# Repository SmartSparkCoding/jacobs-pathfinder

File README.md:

# Jacob's (Amazing) Pathfinder

A Pathfinder, created with Stasis' Guides for Hack Club Stasis (and myself, of course!). I do follow the slides for some of this, even though I am working alone. 

## Pathfinder Session 1 - 1 hour

I created the schemtic for my Pathfinder. I also added my footprints ready for my next session. I am up to Slide 51 on the Workshop Guide. Here is what I did:

## Pathfinder Session 2 - 1 Hour and 15 Minutes

I converted my schematic into my PCB design, making sure that everything works correctly. I also added an extra button as my future plan is to have a three button game and the fourth to reset the game. 

## Pathfinder Session 3 - 1 Hour and 7 Minutes

Almost done! I just added all the 3D models to my PCB and started writing my code for the pathfinder! 

## Pathfinder Session 4 - 1 hour

Spent just 1 hour putting together all my code! Started some of it yesterday and just waiting for a sanity check from Slack!

## Pathfinder Session 5 - 10 Minutes

Made some simple PCB fixes and researched into adding the Hack Club logo to the PCB. Also made some quick changes to the code.

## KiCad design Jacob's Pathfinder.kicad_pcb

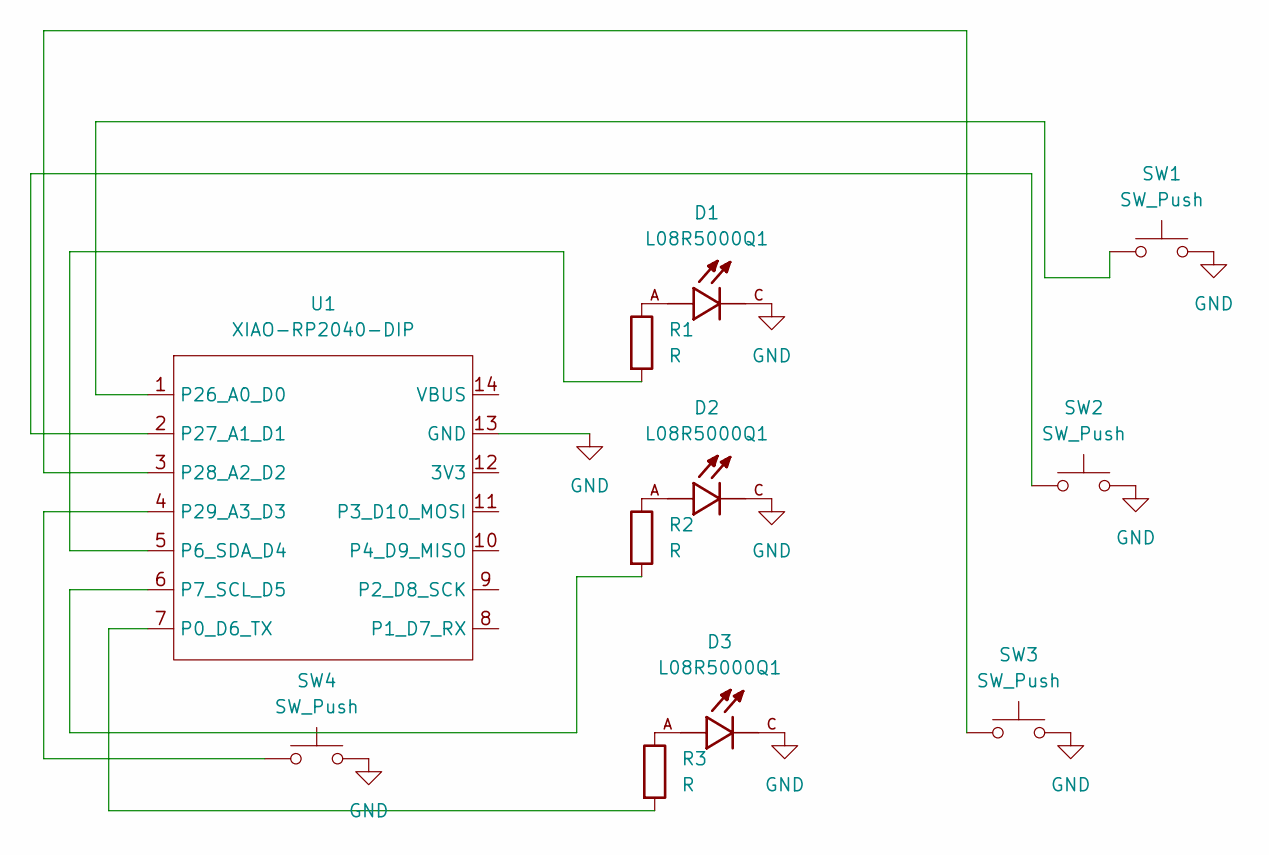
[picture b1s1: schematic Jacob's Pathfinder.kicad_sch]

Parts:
D1, D2, D3: L08R5000Q1; LEDRD254W57D500H1070; PARTREV NA
R1, R2, R3: R; R_Axial_DIN0204_L3.6mm_D1.6mm_P5.08mm_Horizontal
SW1, SW2, SW3, SW4: SW_Push; SW_Cherry_MX_1.00u_PCB
U1: XIAO-RP2040-DIP

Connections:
GND: D1.C, D2.C, D3.C, SW1.2, SW2.2, SW3.2, SW4.2, U1.13 (GND)
unnamed: D1.A, R1.1
unnamed: D2.A, R2.1
unnamed: D3.A, R3.1
unnamed: R3.2, U1.7 (P0_D6_TX)
unnamed: R1.2, U1.5 (P6_SDA_D4)
unnamed: R2.2, U1.6 (P7_SCL_D5)
unnamed: SW1.1, U1.1 (P26_A0_D0)
unnamed: SW2.1, U1.2 (P27_A1_D1)
unnamed: SW3.1, U1.3 (P28_A2_D2)
unnamed: SW4.1, U1.4 (P29_A3_D3)

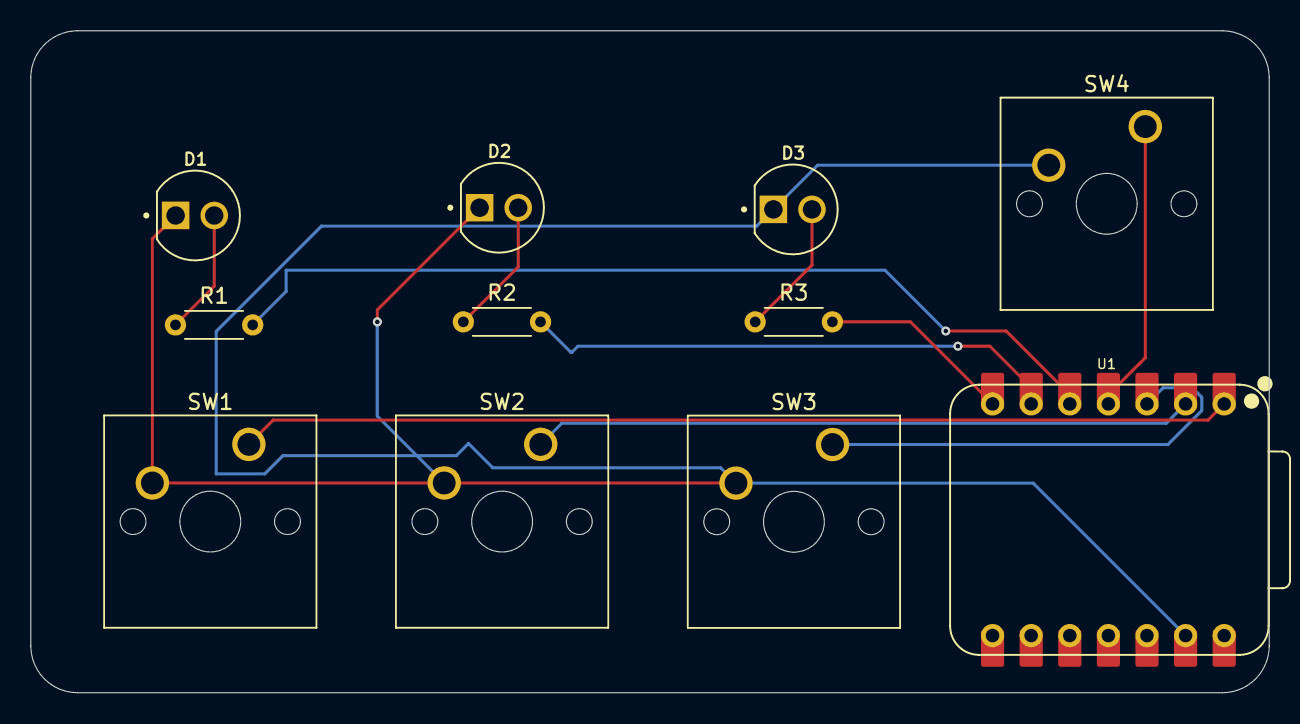
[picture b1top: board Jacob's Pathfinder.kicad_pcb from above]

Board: 2 copper layers, 81.5 x 43.6 mm, 11 parts (0 on the bottom side), 11 nets.

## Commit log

2026-03-29 Revise README title and add session information
    Updated project title and added session details.
2026-03-29 Rename Screenshot 2026-03-29 at 19.14.26.png to session1.png
2026-03-29 Include schematic image in README
    Added a schematic image for Pathfinder Session 1.
2026-03-29 Revise README with session time and progress details
    Updated session duration and added details about progress.
2026-03-31 Update README with PCB design and button details
    Added details about the PCB design and extra button for future plans.
2026-04-01 Session 3 - Updated Files
2026-04-01 Revise Pathfinder session details and add PCB info
    Updated session details and added information about the PCB design and 3D models.
2026-04-01 Session 3 Code
2026-04-02 Document Pathfinder Session 4 progress
    Added details about Pathfinder Session 4 and included screenshots.
2026-04-03 Add Pathfinder Session 5 updates to README
    Documented PCB fixes and code changes in session 5.
